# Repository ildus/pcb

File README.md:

My PCBs
-------

I keep my PCBs here. Feel free to use them.
For now i have:

* Amplifier based on TDA7386, adapted to use with Toyota OEM car stereo connector

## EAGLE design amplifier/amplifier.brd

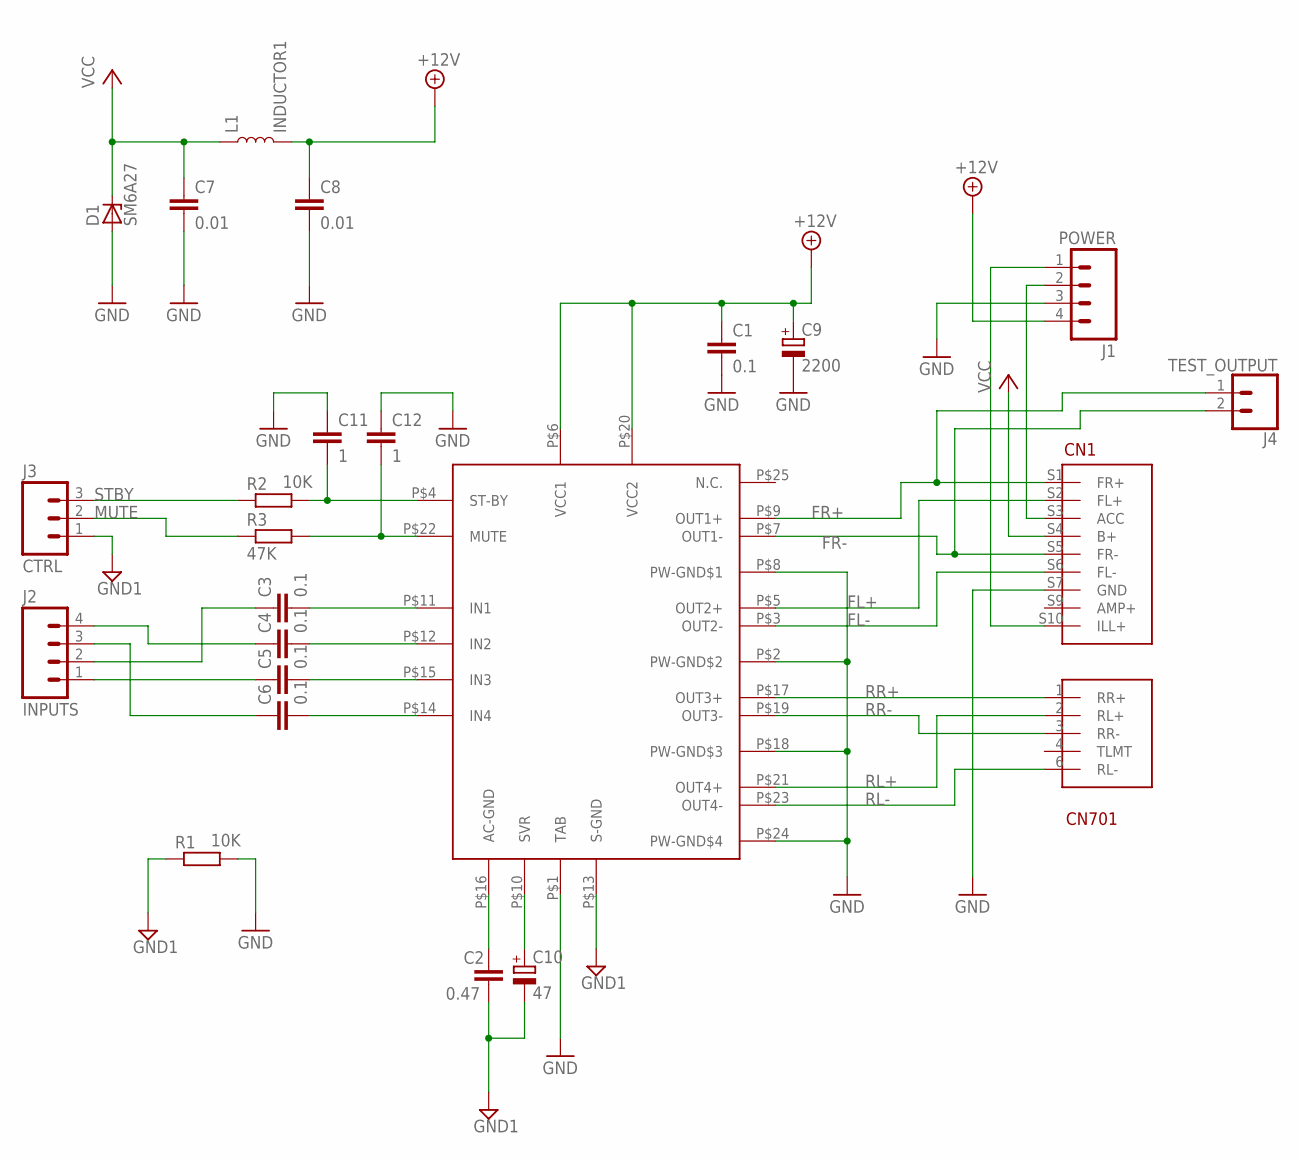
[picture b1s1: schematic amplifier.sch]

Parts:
C1, C3, C4, C5, C6: 0.1; C1206
C2: 0.47; C1206
C7, C8: 0.01; C1206
C9: 2200; E5-10,5
C10: 47; E5-4
C11, C12: 1; C1206
CN1: CN701
D1: SM6A27; DO-218AB
J1: POWER; 1X04_LOCK_LONGPADS
J2: INPUTS; 1X04_LOCK_LONGPADS
J3: CTRL; 1X03_LOCK_LONGPADS@1
J4: TEST_OUTPUT; 1X02_LOCK_LONGPADS
L1: INDUCTOR1
R1, R2: 10K; M1206
R3: 47K; M1206
U$1: TDA7386

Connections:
+12V: C1.1, C8.1, C9.+, J1.4, L1.2, U$1.P$6 (VCC1), U$1.P$20 (VCC2)
AC-GND-IN: C2.1, U$1.P$16 (AC-GND)
ACC: CN1.S3 (ACC), J1.2
FL+: CN1.S2 (FL+), U$1.P$5 (OUT2+)
FL-: CN1.S6 (FL-), U$1.P$3 (OUT2-)
FR+: CN1.S1 (FR+), J4.1, U$1.P$9 (OUT1+)
FR-: CN1.S5 (FR-), J4.2, U$1.P$7 (OUT1-)
GND: C1.2, C7.2, C8.2, C9.-, C11.1, C12.1, CN1.S7 (GND), D1.A, J1.3, R1.2, U$1.P$1 (TAB), U$1.P$2 (PW-GND$2), U$1.P$8 (PW-GND$1), U$1.P$18 (PW-GND$3), U$1.P$24 (PW-GND$4)
GND1: C2.2, C10.-, J3.1, R1.1, U$1.P$13 (S-GND)
ILL+: CN1.S10 (ILL+), J1.1
IN1: C3.1, J2.2
IN2: C4.1, J2.4
IN3: C5.1, J2.1
IN4: C6.1, J2.3
MUTE: J3.2, R3.1
MUTE-IN: C12.2, R3.2, U$1.P$22 (MUTE)
P_IN1: C3.2, U$1.P$11 (IN1)
P_IN2: C4.2, U$1.P$12 (IN2)
P_IN3: C5.2, U$1.P$15 (IN3)
P_IN4: C6.2, U$1.P$14 (IN4)
RL+: CN1.2 (RL+), U$1.P$21 (OUT4+)
RL-: CN1.6 (RL-), U$1.P$23 (OUT4-)
RR+: CN1.1 (RR+), U$1.P$17 (OUT3+)
RR-: CN1.3 (RR-), U$1.P$19 (OUT3-)
STBY: J3.3, R2.1
STBY-IN: C11.2, R2.2, U$1.P$4 (ST-BY)
SVR-IN: C10.+, U$1.P$10 (SVR)
VCC: C7.1, CN1.S4 (B+), D1.C, L1.1

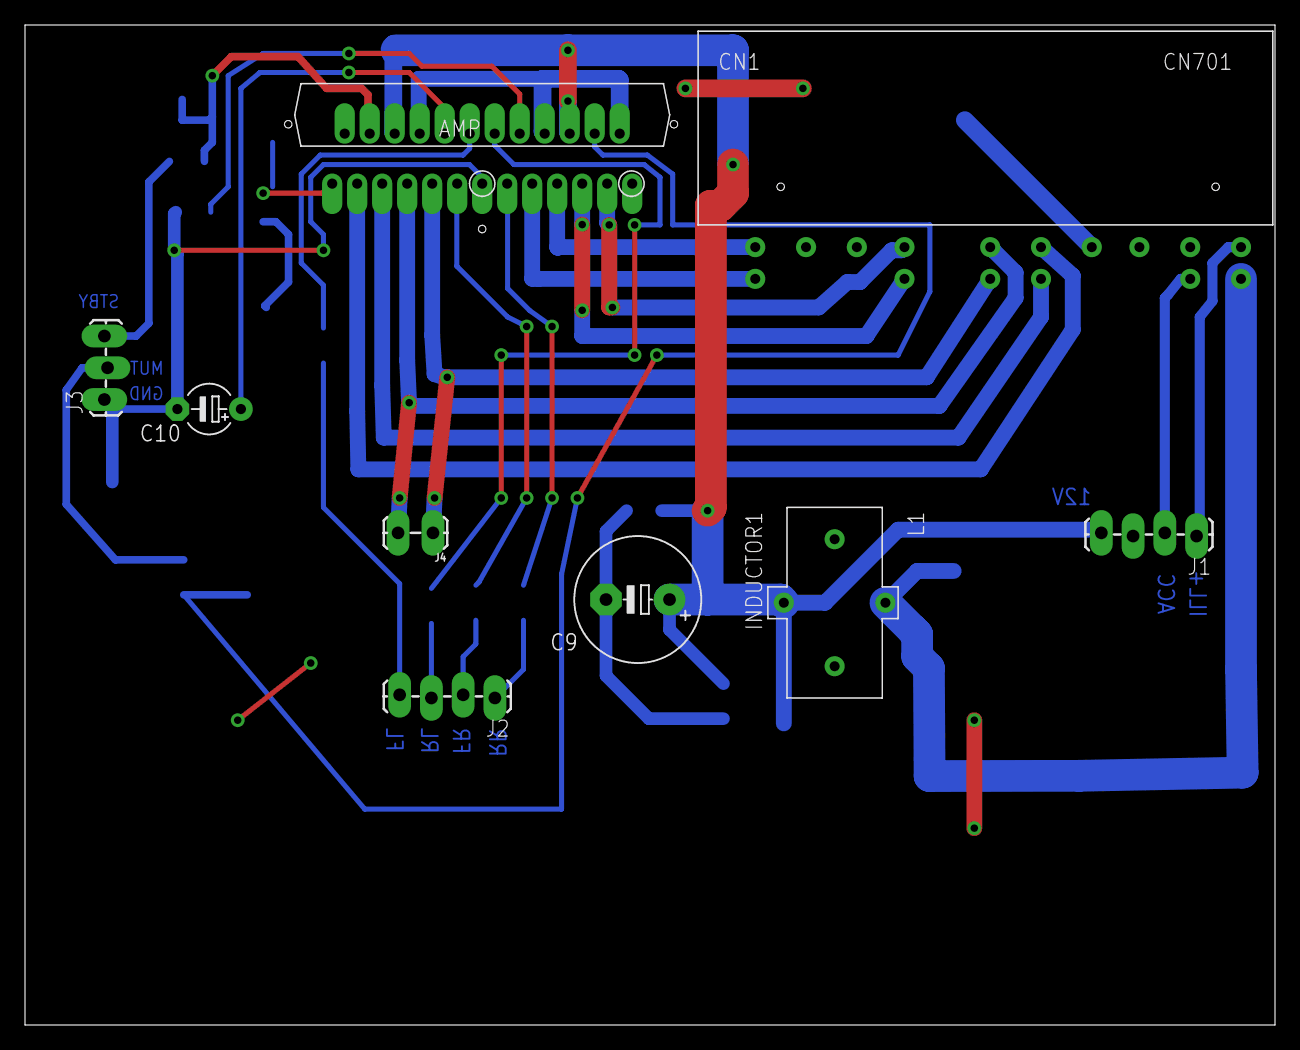
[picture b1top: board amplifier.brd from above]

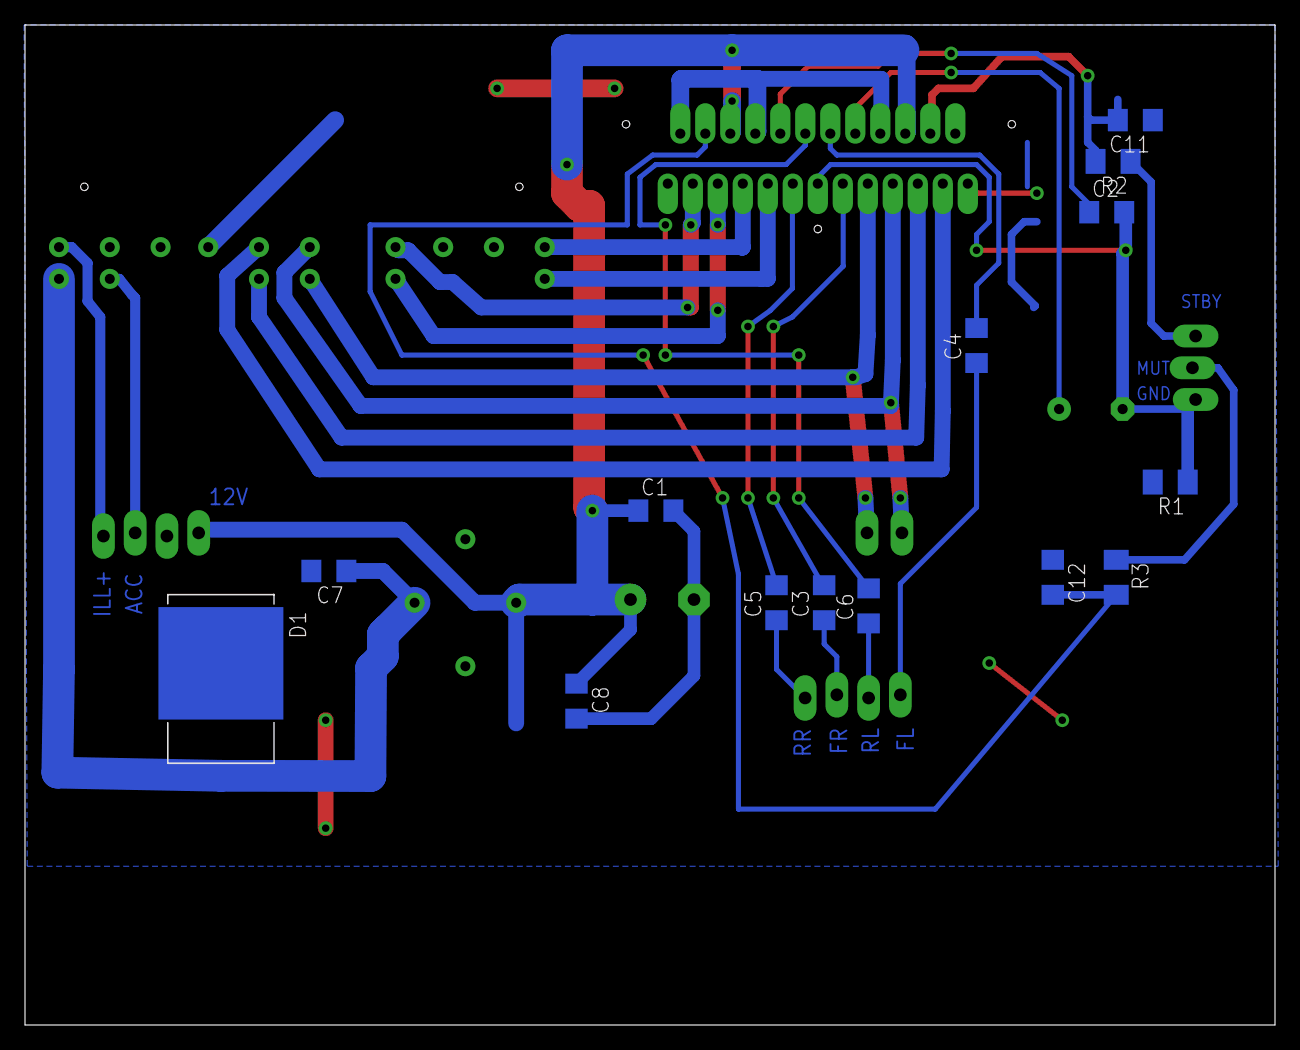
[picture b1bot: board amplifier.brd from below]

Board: 2 copper layers, 100.0 x 80.0 mm, 23 parts (14 on the bottom side), 28 nets.

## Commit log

2017-02-20 Initial
2017-04-16 Add distortion and power controller schematics

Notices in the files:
parts and their libraries:
SparkFun-Connectors: Licensing: Creative Commons ShareAlike 4.0 International - https://creativecommons.org/licenses/by-sa/4.0
